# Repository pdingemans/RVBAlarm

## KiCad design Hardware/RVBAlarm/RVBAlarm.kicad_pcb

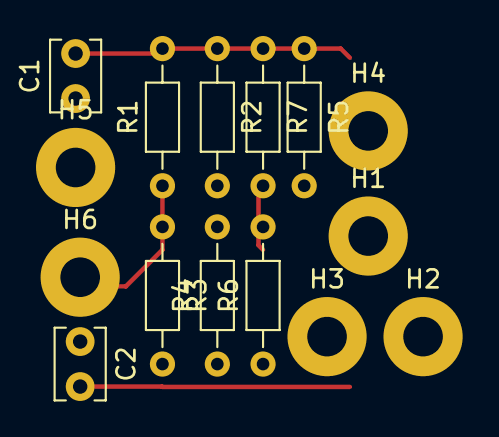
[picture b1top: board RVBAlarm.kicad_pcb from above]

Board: 2 copper layers, 15 parts (0 on the bottom side), 9 nets.

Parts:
C1, C2: 100nF; C_Disc_D3.8mm_W2.6mm_P2.50mm
H1, H2, H3, H4, H5, H6: MountingHole_Pad; MountingHole_2.2mm_M2_Pad
R1, R2, R3, R4: 47K; R_Axial_DIN0204_L3.6mm_D1.6mm_P7.62mm_Horizontal
R5: 22K; R_Axial_DIN0204_L3.6mm_D1.6mm_P7.62mm_Horizontal
R6, R7: 10K; R_Axial_DIN0204_L3.6mm_D1.6mm_P7.62mm_Horizontal

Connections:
+5V: H4.1, R5.1
/A0: H2.1, R6.2
/A1: H3.1, R7.2
/Left: C1.1, H5.1
/Right: C2.1, H6.1
/Vref: H1.1, R1.1, R3.1, R5.2
GND: R2.2, R4.2
unnamed: C1.2, R1.2, R2.1, R7.1
unnamed: C2.2, R3.2, R4.1, R6.1

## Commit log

2023-04-30 adding diagram for testing
2023-04-30 design updated
2023-04-30 deleting statediagram
2023-04-30 edit state diagram in design file
2023-04-30 adding input classes
2023-04-30 inputs to main and pass them to the handler
2023-04-30 added selftransitition to alarm in case a call comes when we;re in alarm
2023-05-02 adding analog and digital inputs
2023-05-02 added state to inputclass
2023-05-02 adapted statediagram, manual inputs added
2023-05-02 completed inout
2023-05-03 completing header
2023-05-06 states uodated
2023-05-07 changed inputs and design
2023-05-15 fixing state and other stuff
2023-05-15 simplify state behaviour
2023-05-15 added ino so it can be compiled with arduion ide
2023-05-15 fix bug in mermaid state
2023-05-22 added movingaverage to analoginputs
2023-05-25 changed analoginput
2023-05-28 update input, polltime stays the same
2024-02-17 fixe spurious alarms
2024-07-11 adding watchdog timer
2025-07-02 fixed analoginput
2025-07-03 fixed levels and convert outut of analoginput to mV
2026-03-23 fixed wraparound millis hangup
2026-03-23 adding HW schematics
2026-03-23 longer waittime at start to charge filter capacitor
2026-03-23 refactored to blink during on ON
2026-03-23 adapted design doc
2026-03-23 converrt puml to mermaid
2026-03-23 refactored naming of state
